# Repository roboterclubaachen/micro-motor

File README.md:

# µMotor: a motor controller for BLDC and DC motors up to 250W

µMotor (or micro-motor) is a motor controller PCB and software made to control any BLDC and DC motor up to 250W.

The micro-motor is supplied with power and CAN bus via a single connector and can control the motor independently.
In addition, a limit switch can be read out and the temperature of the motor can be monitored.

Communication is done via Can-Bus using CANopen protocol.

The software is written using the [modm.io](https://modm.io/) framework and [librobots2](https://github.com/roboterclubaachen/librobots2).

For more information read the following blog posts about the project (in German):
* [µMotor: Idee](http://www.roboterclub.rwth-aachen.de/blog/2018/micro-motor-motorcontroller.html)
* [µMotor: Inbetriebnahme und Debugging](http://www.roboterclub.rwth-aachen.de/blog/2018/micro-motor-debugging-inbetriebnahme.html)
* [µMotor 2 - Teil 1: Konzept](http://www.roboterclub.rwth-aachen.de/blog/2019/micro-motor-2-teil-1.html)
* [µMotor 2 - Teil 2: Strommessung](http://www.roboterclub.rwth-aachen.de/blog/2019/micro-motor-2-teil-2.html)
* [µMotor 2 - Teil 3: Microcontroller & Stromversorgung](http://www.roboterclub.rwth-aachen.de/blog/2019/micro-motor-2-teil-3.html)
* [µMotor 2 - Teil 4: Strom- und Spannungsmessung mit ADC](https://www.roboterclub.rwth-aachen.de/blog/2020/micro-motor-2-teil-4.html)

## Technical data
* 3 phases (BLDC and DC motors)
* Approx. 10A per phase (with precise current measurement)
* 24V nominal operating voltage
* Adjustable cycle-by-cycle current limiting (short circuit protection)
* CAN bus
    * CAN-FD supported
    * CANopen protocoll (partial implemented)
* AB(I) incremental encoder connector
* Hall sensor connector
* Temperature sensor (NTC) connector
* Limit switch (GPIO) connector
* LEDs for status and diagnosis
* Configurable ID (from STM32 hardware ID)
* Easy to solder and assemble

## Status

PCBs *micro-motor-v1 (rev1)* and *macro-motor* are not supported anymore.

The second version *micro-motor-v2* is basically functional, software improvements are in progress.

PCB _micro-motor-v2.1_ is similar to _v2_, but with added RC filters at encoder connector,
added 1 µF capacitor to the STM32 _VREFBUF_ output and changed DC/DC converter modules (caused by component shortage).

Software at HEAD is compatible with micro-motor-v2.\[0,1,2\], however the correct version needs to be selected in the project.xml to account for hardware differences with "Board.v2_1" being compatible with v2.0, and v2.1 and "Board.v2_2" being compatible with v2.2.

## Folder structure

#### `kicad/pcb_name/`
* KiCad files of the PCBs

#### `STM32CubeMX/`
* Pinout configuration of the STM32 microcontrollers done with [STs CubeMX software](https://www.st.com/en/development-tools/stm32cubemx.html)

#### `tests/`
* Test software. Useful during PCB assembly

#### `app/`
* Main Software

#### `src/`
* Common files used between main software and tests.

## Notes

### On first boot
When first assembled the boards will be stuck inside the STM32 bootloader because BOOT0 is used as a GPIO pin.
This behaviour can be overwritten by setting an option byte: \
First read flash option byte:

    openocd -f interface/stlink.cfg -c "transport select hla_swd" -f target/stm32g4x.cfg -c "reset_config none" -c "init" -c "stm32g4x option_read 0 0x20" -c "shutdown"

Should respond 'Option Register: <0x40022020> = 0xffeff8aa' on a new PCB
or 'Option Register: <0x40022020> = 0xfbeff8aa' once the nSWBOOT0 bit is cleared. \
Clear the bit:

    openocd -f interface/stlink.cfg -c "transport select hla_swd" -f target/stm32g4x.cfg -c "reset_config none" -c "init" -c "stm32g4x option_write 0 0x20 0x00000000 0x04000000" -c "shutdown"

## License

Software is licensed under [GPLv3](LICENSE).
Hardware (PCB files, ...) is licensed under [CERN OHL v.1.2](LICENSE.hardware).

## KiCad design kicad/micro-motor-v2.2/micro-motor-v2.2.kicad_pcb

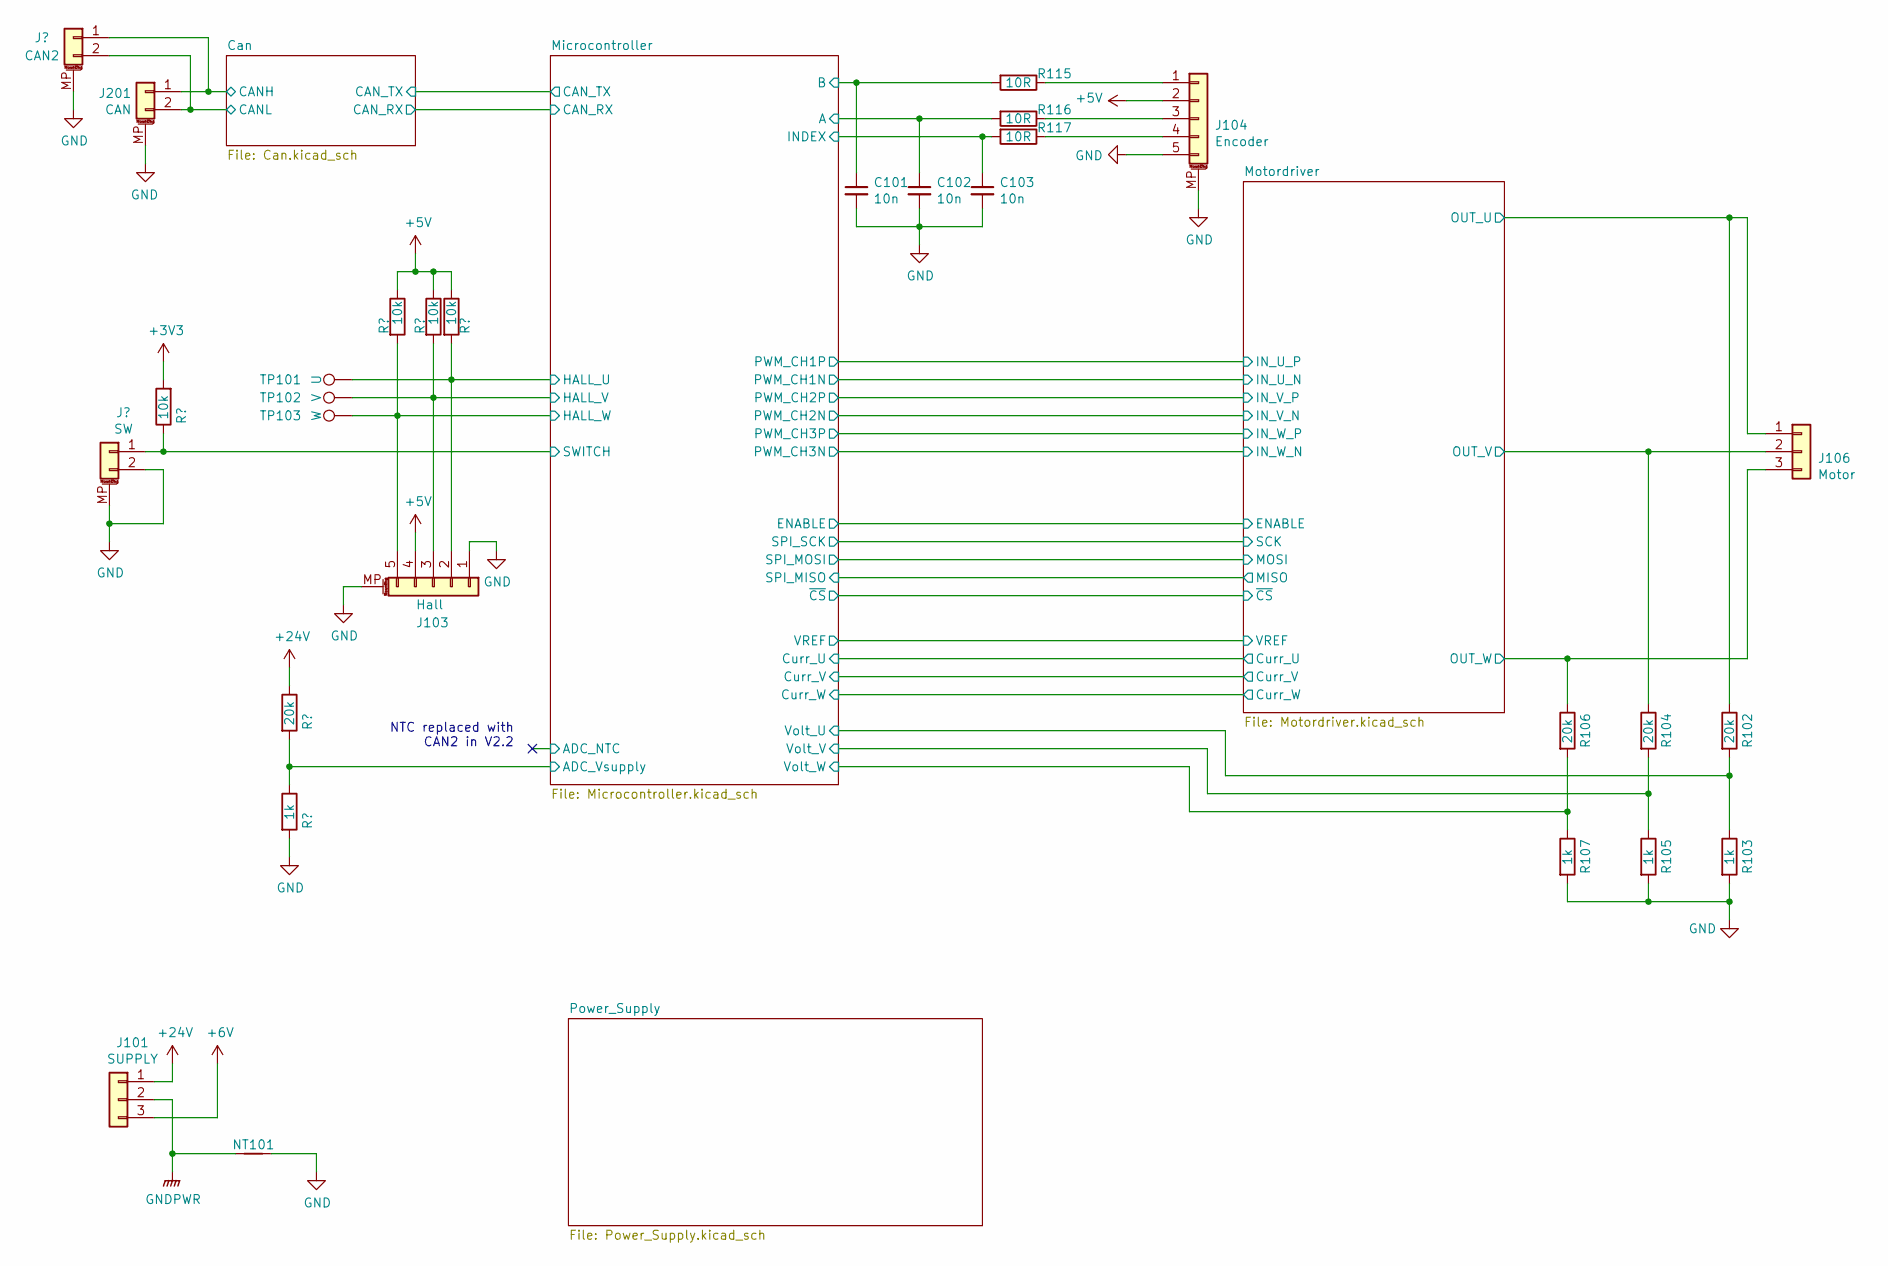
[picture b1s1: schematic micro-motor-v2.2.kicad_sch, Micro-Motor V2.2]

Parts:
C101, C102, C103: 10n; C_0402_1005Metric
J101: SUPPLY; JST_XH_B3B-XH-A_1x03_P2.50mm_Vertical
J102: SW; JST_GH_BM02B-GHS-TBT_1x02-1MP_P1.25mm_Vertical
J103: Hall; JST_GH_BM05B-GHS-TBT_1x05-1MP_P1.25mm_Vertical
J104: Encoder; JST_GH_BM05B-GHS-TBT_1x05-1MP_P1.25mm_Vertical
J105: CAN2; JST_GH_BM02B-GHS-TBT_1x02-1MP_P1.25mm_Vertical
J106: Motor; JST_XH_B3B-XH-A_1x03_P2.50mm_Vertical
J201: CAN; JST_GH_BM02B-GHS-TBT_1x02-1MP_P1.25mm_Vertical
NT101: NetTie_2; NetTie-2_SMD_Pad0.5mm
R101, R111, R112, R113: 10k; R_0402_1005Metric
R102, R104, R106, R109: 20k; R_0402_1005Metric
R103, R105, R107, R110: 1k; R_0402_1005Metric
R115, R116, R117: 10R; R_0402_1005Metric
TP101: U; TestPoint_Pad_D1.0mm
TP102: V; TestPoint_Pad_D1.0mm
TP103: W; TestPoint_Pad_D1.0mm

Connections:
+3V3: R101.2; also elsewhere on the board
+5V: J103.4, J104.2, R111.1, R112.1, R113.1; also elsewhere on the board
+6V: J101.3; also elsewhere on the board
+24V: J101.1, R109.1; also elsewhere on the board
/Can/CANH: J105.1; also elsewhere on the board
/Can/CANL: J105.2; also elsewhere on the board
/Microcontroller/A: C102.1, R116.2; also elsewhere on the board
/Microcontroller/ADC_Vsupply: R109.2, R110.1; also elsewhere on the board
/Microcontroller/B: C101.1, R115.2; also elsewhere on the board
/Microcontroller/HALL_U: J103.2, R113.2, TP101.1; also elsewhere on the board
/Microcontroller/HALL_V: J103.3, R112.2, TP102.1; also elsewhere on the board
/Microcontroller/HALL_W: J103.5, R111.2, TP103.1; also elsewhere on the board
/Microcontroller/INDEX: C103.1, R117.2; also elsewhere on the board
/Microcontroller/SWITCH: J102.1, R101.1; also elsewhere on the board
/Microcontroller/Volt_U: R102.2, R103.1; also elsewhere on the board
/Microcontroller/Volt_V: R104.2, R105.1; also elsewhere on the board
/Microcontroller/Volt_W: R106.2, R107.1; also elsewhere on the board
/Motordriver/OUT_U: J106.1, R102.1; also elsewhere on the board
/Motordriver/OUT_V: J106.2, R104.1; also elsewhere on the board
/Motordriver/OUT_W: J106.3, R106.1; also elsewhere on the board
GND: C101.2, C102.2, C103.2, J102.2, J102.MP (MountPin), J103.1, J103.MP (MountPin), J104.5, J104.MP (MountPin), J105.MP (MountPin), NT101.2, R103.2, R105.2, R107.2, R110.2; also elsewhere on the board
GNDPWR: J101.2, NT101.1; also elsewhere on the board
unnamed: J104.1, R115.1
unnamed: J104.3, R116.1
unnamed: J104.4, R117.1

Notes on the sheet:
NTC replaced with CAN2 in V2.2

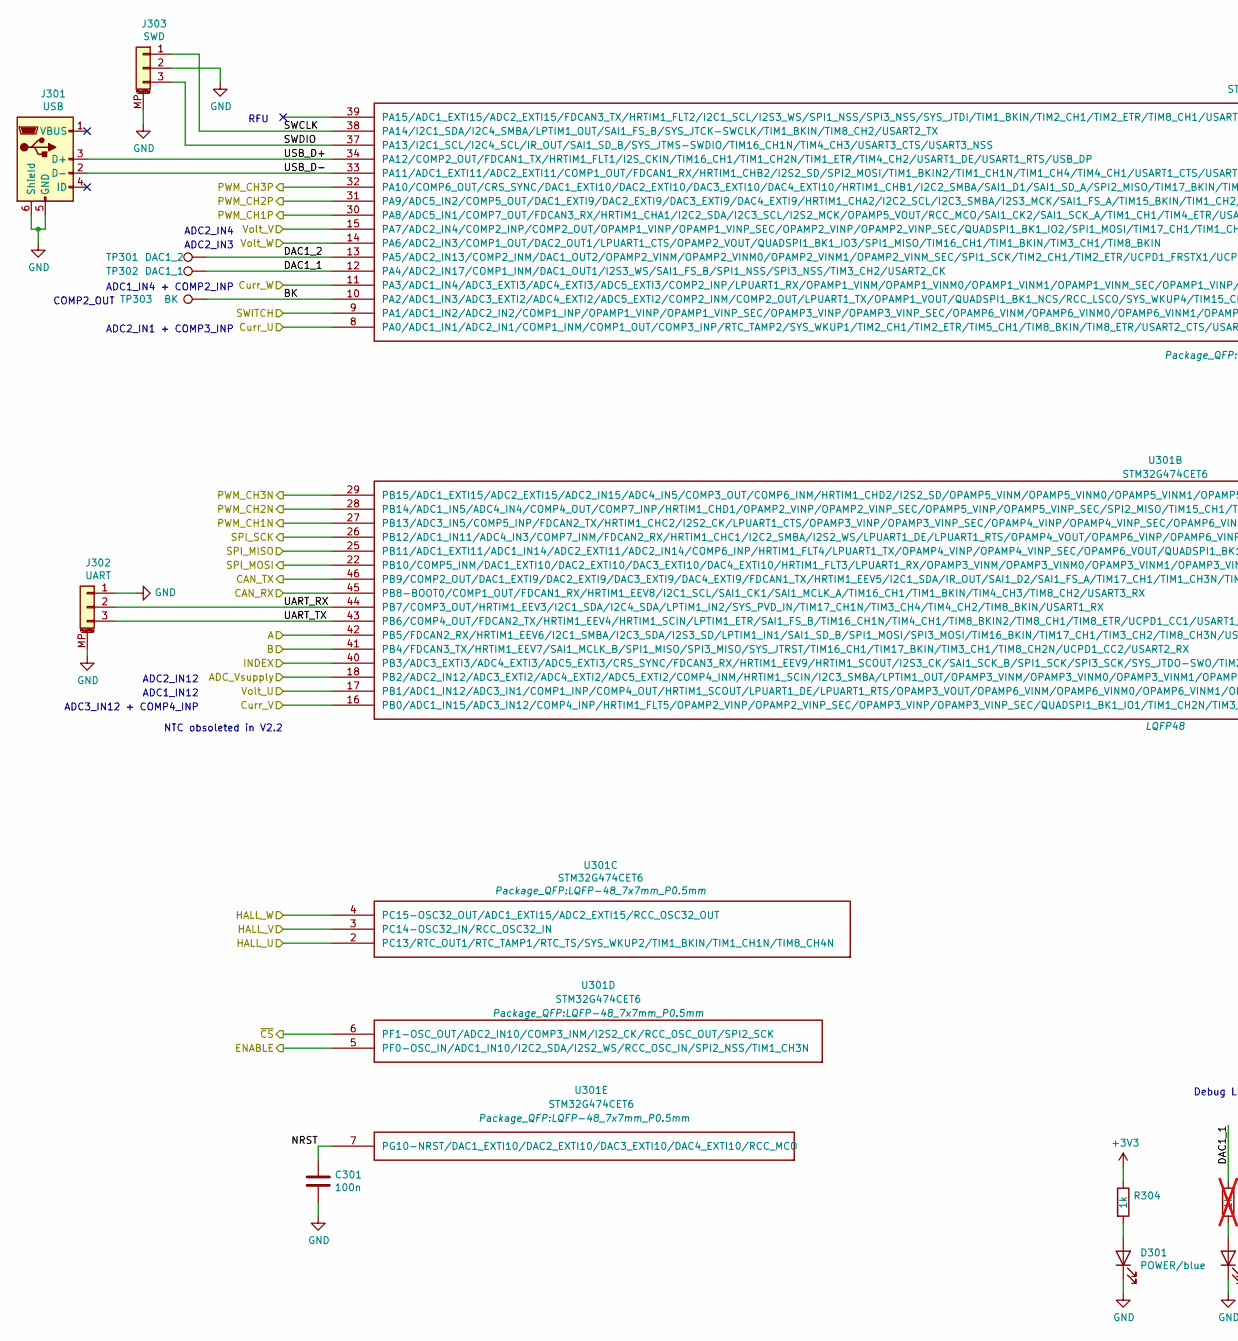
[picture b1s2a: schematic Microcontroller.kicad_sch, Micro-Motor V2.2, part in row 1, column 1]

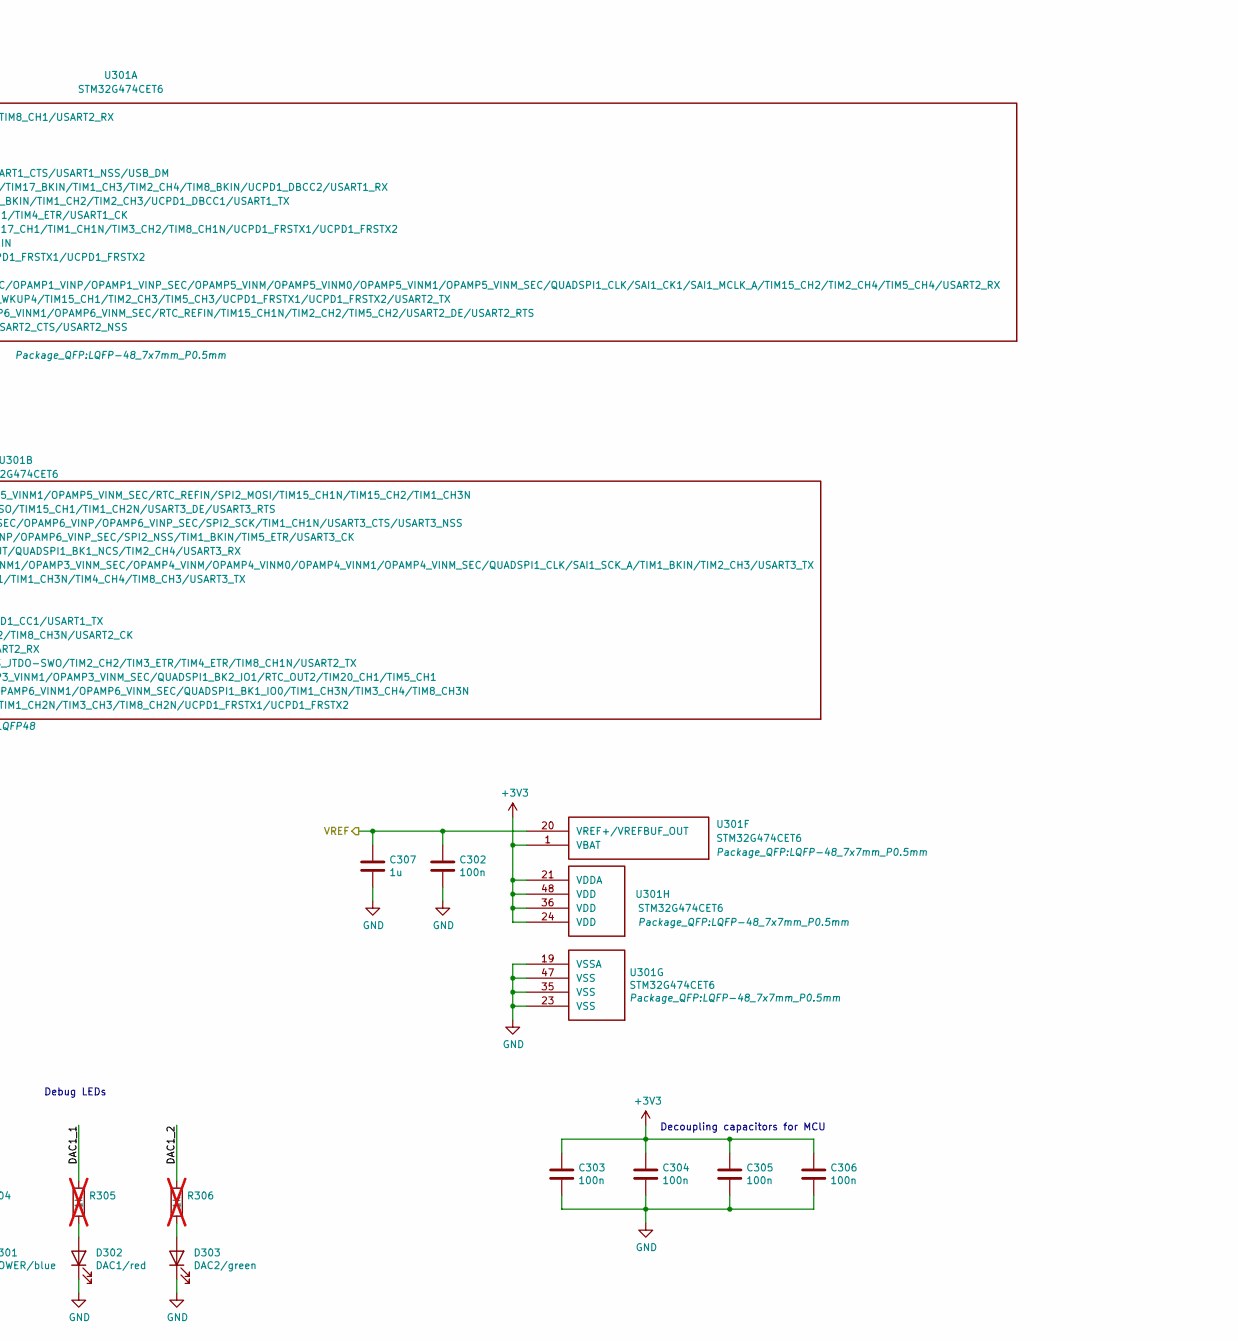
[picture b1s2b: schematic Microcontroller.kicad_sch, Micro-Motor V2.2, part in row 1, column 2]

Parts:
C301, C302, C303, C304, C305, C306: 100n; C_0402_1005Metric
C307: 1u; C_0402_1005Metric
D301: POWER/blue; LED_0402_1005Metric
D302: DAC1/red; LED_0402_1005Metric
D303: DAC2/green; LED_0402_1005Metric
J301: USB; USB_Micro-B_Molex-105133-0001
J302: UART; JST_GH_BM03B-GHS-TBT_1x03-1MP_P1.25mm_Vertical
J303: SWD; JST_GH_BM03B-GHS-TBT_1x03-1MP_P1.25mm_Vertical
R304: 1k; R_0402_1005Metric
R305, R306: 1k; R_0402_1005Metric; not fitted
TP301: DAC1_2; TestPoint_Pad_D1.0mm
TP302: DAC1_1; TestPoint_Pad_D1.0mm
TP303: BK; TestPoint_Pad_D1.0mm
U301: STM32G474CET6; LQFP-48_7x7mm_P0.5mm

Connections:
+3V3: C303.1, C304.1, C305.1, C306.1, R304.1, U301.1 (VBAT), U301.21 (VDDA), U301.24 (VDD), U301.36 (VDD), U301.48 (VDD); also elsewhere on the board
/Can/CAN_RX: U301.45 (PB8-BOOT0/COMP1_OUT/FDCAN1_RX/HRTIM1_EE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); also elsewhere on the board
/Can/CAN_TX: U301.46 (PB9/COMP2_OUT/DAC1_EXTI9/DAC2_EXTI9/DAC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); also elsewhere on the board
/Microcontroller/A: U301.42 (PB5/FDCAN2_RX/HRTIM1_EEV6/I2C1_SMBA/I2C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); also elsewhere on the board
/Microcontroller/ADC_Vsupply: U301.18 (PB2/ADC2_IN12/ADC3_EXTI2/ADC4_EXTI2/ADC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); also elsewhere on the board
/Microcontroller/B: U301.41 (PB4/FDCAN3_TX/HRTIM1_EEV7/SAI1_MCLK_B/S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); also elsewhere on the board
/Microcontroller/BK: TP303.1, U301.10 (PA2/ADC1_IN3/ADC3_EXTI2/ADC4_EXTI2/ADC5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)
/Microcontroller/Curr_U: U301.8 (PA0/ADC1_IN1/ADC2_IN1/COMP1_INM/COMP1_O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); also elsewhere on the board
/Microcontroller/Curr_V: U301.16 (PB0/ADC1_IN15/ADC3_IN12/COMP4_INP/HRTIM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); also elsewhere on the board
/Microcontroller/Curr_W: U301.11 (PA3/ADC1_IN4/ADC3_EXTI3/ADC4_EXTI3/ADC5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); also elsewhere on the board
/Microcontroller/DAC1_1: R305.1, TP302.1, U301.12 (PA4/ADC2_IN17/COMP1_INM/DAC1_OUT1/I2S3_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)
/Microcontroller/DAC1_2: R306.1, TP301.1, U301.13 (PA5/ADC2_IN13/COMP2_INM/DAC1_OUT2/OPAMP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)
/Microcontroller/ENABLE: U301.5 (PF0-OSC_IN/ADC1_IN10/I2C2_SDA/I2S2_WS/R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); also elsewhere on the board
/Microcontroller/HALL_U: U301.2 (PC13/RTC_OUT1/RTC_TAMP1/RTC_TS/SYS_WKUP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); also elsewhere on the board
/Microcontroller/HALL_V: U301.3 (PC14-OSC32_IN/RCC_OSC32_IN); also elsewhere on the board
/Microcontroller/HALL_W: U301.4 (PC15-OSC32_OUT/ADC1_EXTI15/ADC2_EXTI15/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); also elsewhere on the board
/Microcontroller/INDEX: U301.40 (PB3/ADC3_EXTI3/ADC4_EXTI3/ADC5_EXTI3/CR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); also elsewhere on the board
/Microcontroller/NRST: C301.1, U301.7 (PG10-NRST/DAC1_EXTI10/DAC2_EXTI10/DAC3_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)
/Microcontroller/PWM_CH1N: U301.27 (PB13/ADC3_IN5/COMP5_INP/FDCAN2_TX/HRTIM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); also elsewhere on the board
/Microcontroller/PWM_CH1P: U301.30 (PA8/ADC5_IN1/COMP7_OUT/FDCAN3_RX/HRTIM1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); also elsewhere on the board
/Microcontroller/PWM_CH2N: U301.28 (PB14/ADC1_IN5/ADC4_IN4/COMP4_OUT/COMP7_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); also elsewhere on the board
/Microcontroller/PWM_CH2P: U301.31 (PA9/ADC5_IN2/COMP5_OUT/DAC1_EXTI9/DAC2_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); also elsewhere on the board
/Microcontroller/PWM_CH3N: U301.29 (PB15/ADC1_EXTI15/ADC2_EXTI15/ADC2_IN15/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); also elsewhere on the board
/Microcontroller/PWM_CH3P: U301.32 (PA10/COMP6_OUT/CRS_SYNC/DAC1_EXTI10/DAC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); also elsewhere on the board
/Microcontroller/SPI_MISO: U301.25 (PB11/ADC1_EXTI11/ADC1_IN14/ADC2_EXTI11/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); also elsewhere on the board
/Microcontroller/SPI_MOSI: U301.22 (PB10/COMP5_INM/DAC1_EXTI10/DAC2_EXTI10/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); also elsewhere on the board
/Microcontroller/SPI_SCK: U301.26 (PB12/ADC1_IN11/ADC4_IN3/COMP7_INM/FDCAN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); also elsewhere on the board
/Microcontroller/SWCLK: J303.1, U301.38 (PA14/I2C1_SDA/I2C4_SMBA/LPTIM1_OUT/SAI1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)
/Microcontroller/SWDIO: J303.3, U301.37 (PA13/I2C1_SCL/I2C4_SCL/IR_OUT/SAI1_SD_B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)
/Microcontroller/SWITCH: U301.9 (PA1/ADC1_IN2/ADC2_IN2/COMP1_INP/OPAMP1_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); also elsewhere on the board
/Microcontroller/UART_RX: J302.2, U301.44 (PB7/COMP3_OUT/HRTIM1_EEV3/I2C1_SDA/I2C4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)
/Microcontroller/UART_TX: J302.3, U301.43 (PB6/COMP4_OUT/FDCAN2_TX/HRTIM1_EEV4/HRT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)
/Microcontroller/USB_D+: J301.3 (D+), U301.34 (PA12/COMP2_OUT/FDCAN1_TX/HRTIM1_FLT1/I2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)
/Microcontroller/USB_D-: J301.2 (D-), U301.33 (PA11/ADC1_EXTI11/ADC2_EXTI11/COMP1_OUT/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)
/Microcontroller/VREF: C302.1, C307.1, U301.20 (VREF+/VREFBUF_OUT); also elsewhere on the board
/Microcontroller/Volt_U: U301.17 (PB1/ADC1_IN12/ADC3_IN1/COMP1_INP/COMP4_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); also elsewhere on the board
/Microcontroller/Volt_V: U301.15 (PA7/ADC2_IN4/COMP2_INP/COMP2_OUT/OPAMP1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); also elsewhere on the board
/Microcontroller/Volt_W: U301.14 (PA6/ADC2_IN3/COMP1_OUT/DAC2_OUT1/LPUART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); also elsewhere on the board
/Microcontroller/~CS: U301.6 (PF1-OSC_OUT/ADC2_IN10/COMP3_INM/I2S2_CK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); also elsewhere on the board
GND: C301.2, C302.2, C303.2, C304.2, C305.2, C306.2, C307.2, D301.1 (K), D302.1 (K), D303.1 (K), J301.5 (GND), J301.6 (Shield), J302.1, J302.MP (MountPin), J303.2, J303.MP (MountPin), U301.19 (VSSA), U301.23 (VSS), U301.35 (VSS), U301.47 (VSS); also elsewhere on the board
unnamed: D301.2 (A), R304.2
unnamed: D302.2 (A), R305.2
unnamed: D303.2 (A), R306.2

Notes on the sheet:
ADC1_IN4 + COMP2_INP
ADC2_IN3
ADC2_IN12
ADC3_IN12 + COMP4_INP
ADC2_IN4
NTC obsoleted in V2.2
Debug LEDs
Decoupling capacitors for MCU
COMP2_OUT
RFU
ADC1_IN12
ADC2_IN1 + COMP3_INP

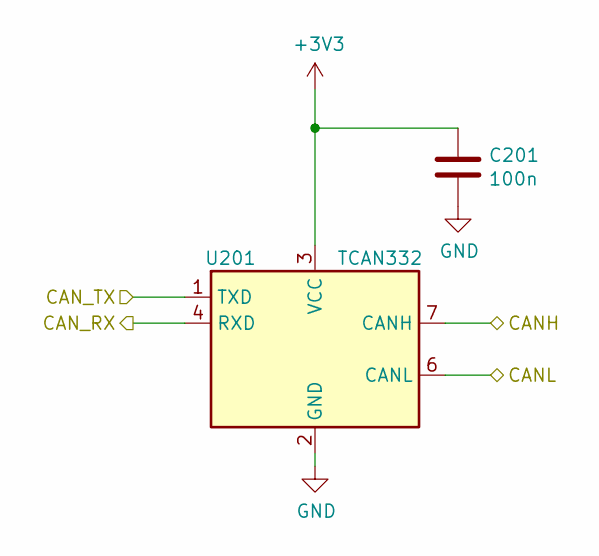
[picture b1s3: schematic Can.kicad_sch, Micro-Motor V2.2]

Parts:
C201: 100n; C_0402_1005Metric
U201: TCAN332; SOT-23-8

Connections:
+3V3: C201.1, U201.3 (VCC); also elsewhere on the board
/Can/CANH: U201.7 (CANH); also elsewhere on the board
/Can/CANL: U201.6 (CANL); also elsewhere on the board
/Can/CAN_RX: U201.4 (RXD); also elsewhere on the board
/Can/CAN_TX: U201.1 (TXD); also elsewhere on the board
GND: C201.2, U201.2 (GND); also elsewhere on the board

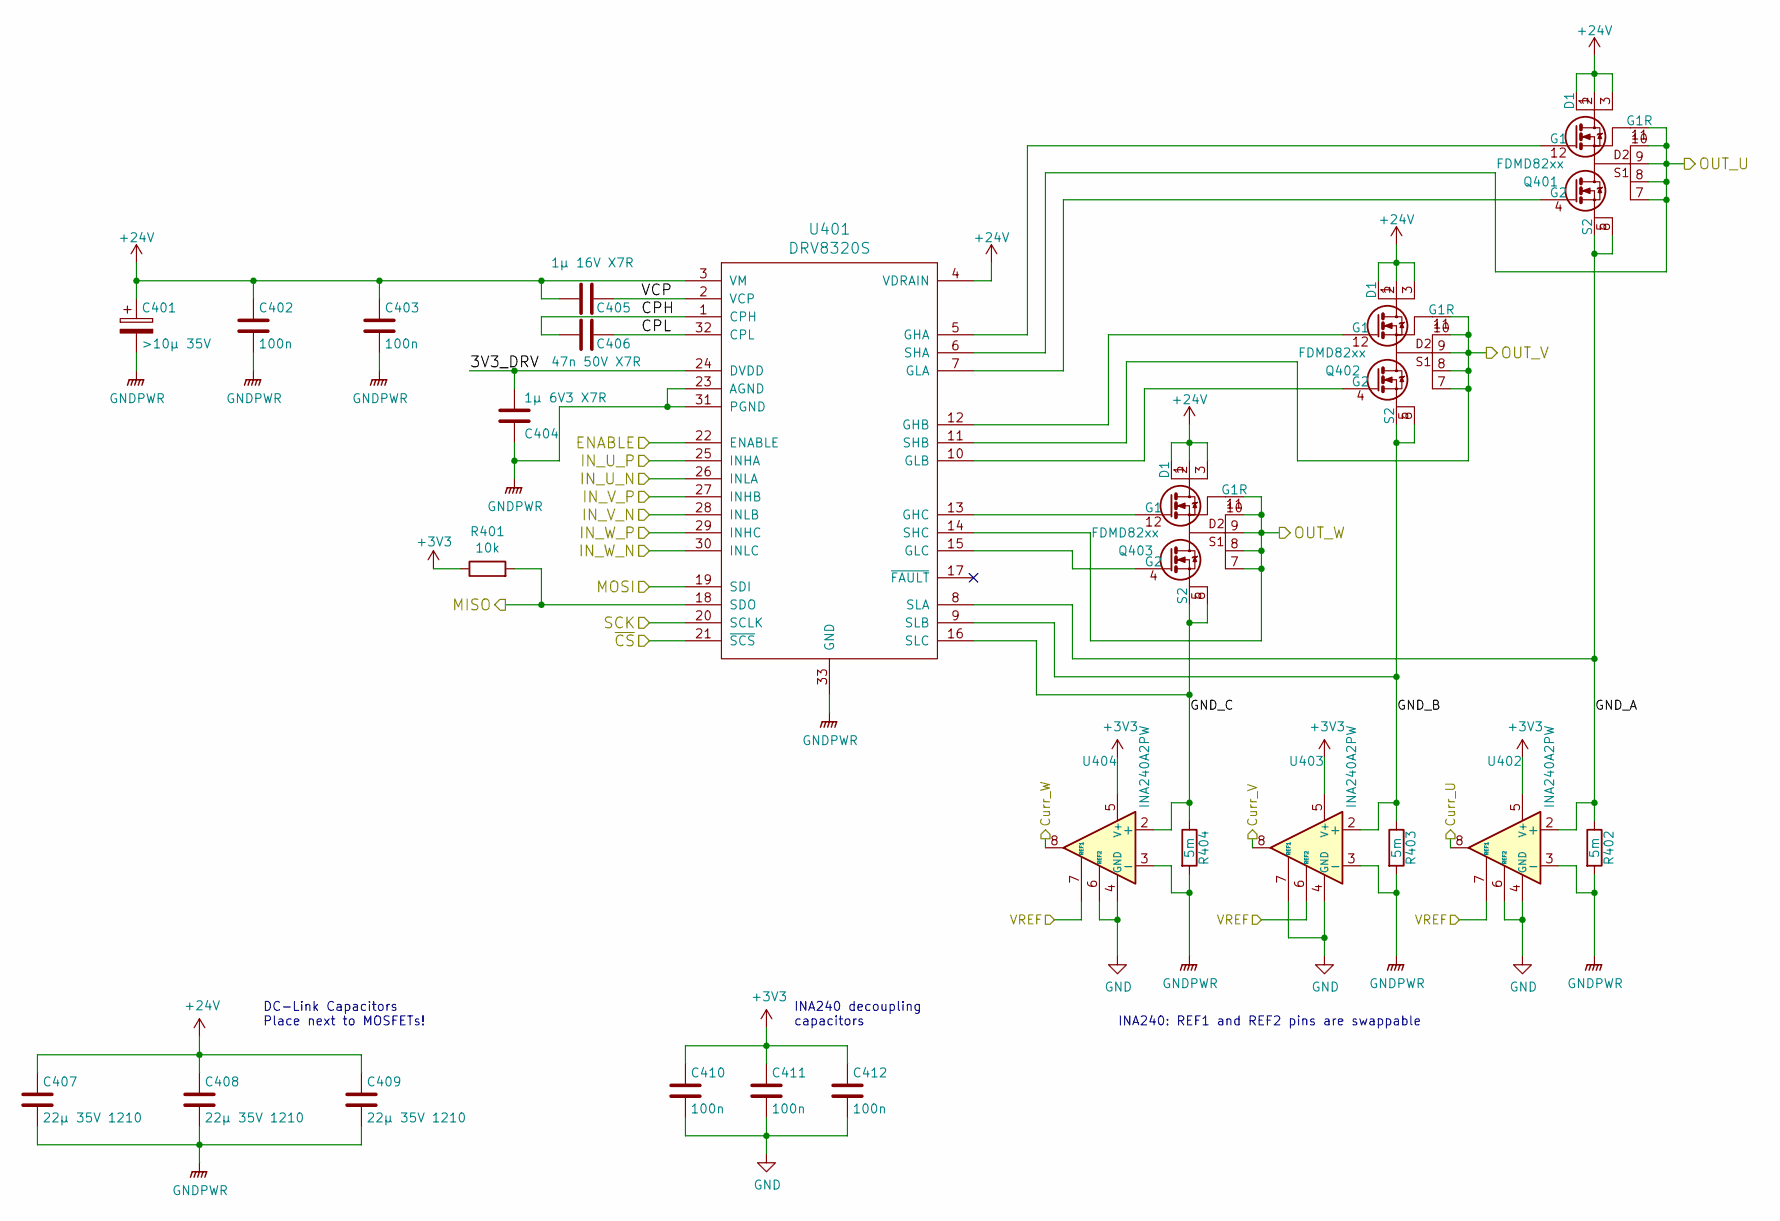
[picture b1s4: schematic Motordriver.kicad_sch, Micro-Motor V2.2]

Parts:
C401: >10µ 35V; CP_Radial_D10.0mm_P5.00mm
C402, C403, C410, C411, C412: 100n; C_0402_1005Metric
C404: 1µ 6V3 X7R; C_0603_1608Metric
C405: 1µ 16V X7R; C_0603_1608Metric
C406: 47n 50V X7R; C_0402_1005Metric
C407, C408, C409: 22µ 35V 1210; C_1210_3225Metric
Q401, Q402, Q403: FDMD82xx; DFN-12-2EP_3.3x5mm_Pitch0.65mm
R401: 10k; R_0402_1005Metric
R402, R403, R404: 5m; R_0805_2012Metric
U401: DRV8320S; QFN-32-1EP_5x5mm_P0.5mm_EP3.45x3.45mm
U402, U403, U404: INA240A2PW; TSSOP-8_4.4x3mm_P0.65mm

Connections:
+3V3: C410.1, C411.1, C412.1, R401.1, U402.5 (V+), U403.5 (V+), U404.5 (V+); also elsewhere on the board
+24V: C401.1, C402.1, C403.1, C405.2, C407.1, C408.1, C409.1, Q401.1 (D1), Q401.2, Q401.3, Q401.13 (D1), Q402.1 (D1), Q402.2, Q402.3, Q402.13 (D1), Q403.1 (D1), Q403.2, Q403.3, Q403.13 (D1), U401.3 (VM), U401.4 (VDRAIN); also elsewhere on the board
/Microcontroller/Curr_U: U402.8; also elsewhere on the board
/Microcontroller/Curr_V: U403.8; also elsewhere on the board
/Microcontroller/Curr_W: U404.8; also elsewhere on the board
/Microcontroller/ENABLE: U401.22 (ENABLE); also elsewhere on the board
/Microcontroller/PWM_CH1N: U401.26 (INLA); also elsewhere on the board
/Microcontroller/PWM_CH1P: U401.25 (INHA); also elsewhere on the board
/Microcontroller/PWM_CH2N: U401.28 (INLB); also elsewhere on the board
/Microcontroller/PWM_CH2P: U401.27 (INHB); also elsewhere on the board
/Microcontroller/PWM_CH3N: U401.30 (INLC); also elsewhere on the board
/Microcontroller/PWM_CH3P: U401.29 (INHC); also elsewhere on the board
/Microcontroller/SPI_MISO: R401.2, U401.18 (SDO); also elsewhere on the board
/Microcontroller/SPI_MOSI: U401.19 (SDI); also elsewhere on the board
/Microcontroller/SPI_SCK: U401.20 (SCLK); also elsewhere on the board
/Microcontroller/VREF: U402.7 (REF1), U403.6 (REF2), U404.7 (REF1); also elsewhere on the board
/Microcontroller/~CS: U401.21 (~SCS); also elsewhere on the board
/Motordriver/3V3_DRV: C404.1, U401.24 (DVDD)
/Motordriver/CPH: C406.2, U401.1 (CPH)
/Motordriver/CPL: C406.1, U401.32 (CPL)
/Motordriver/GND_A: Q401.5 (S2), Q401.6, Q401.14 (S2), R402.1, U401.8 (SLA), U402.2 (+)
/Motordriver/GND_B: Q402.5 (S2), Q402.6, Q402.14 (S2), R403.1, U401.9 (SLB), U403.2 (+)
/Motordriver/GND_C: Q403.5 (S2), Q403.6, Q403.14 (S2), R404.1, U401.16 (SLC), U404.2 (+)
/Motordriver/OUT_U: Q401.7, Q401.8, Q401.9, Q401.10, Q401.11 (G1R), U401.6 (SHA); also elsewhere on the board
/Motordriver/OUT_V: Q402.7, Q402.8, Q402.9, Q402.10, Q402.11 (G1R), U401.11 (SHB); also elsewhere on the board
/Motordriver/OUT_W: Q403.7, Q403.8, Q403.9, Q403.10, Q403.11 (G1R), U401.14 (SHC); also elsewhere on the board
/Motordriver/VCP: C405.1, U401.2 (VCP)
GND: C410.2, C411.2, C412.2, U402.1 (GND), U402.4 (GND), U402.6 (REF2), U403.1 (GND), U403.4 (GND), U403.7 (REF1), U404.1 (GND), U404.4 (GND), U404.6 (REF2); also elsewhere on the board
GNDPWR: C401.2, C402.2, C403.2, C404.2, C407.2, C408.2, C409.2, R402.2, R403.2, R404.2, U401.23 (AGND), U401.31 (PGND), U401.33 (GND), U402.3 (-), U403.3 (-), U404.3 (-); also elsewhere on the board
unnamed: Q401.12 (G1), U401.5 (GHA)
unnamed: Q401.4 (G2), U401.7 (GLA)
unnamed: Q402.12 (G1), U401.12 (GHB)
unnamed: Q402.4 (G2), U401.10 (GLB)
unnamed: Q403.12 (G1), U401.13 (GHC)
unnamed: Q403.4 (G2), U401.15 (GLC)

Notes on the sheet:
DC-Link Capacitors Place next to MOSFETs!
INA240 decoupling capacitors
INA240: REF1 and REF2 pins are swappable

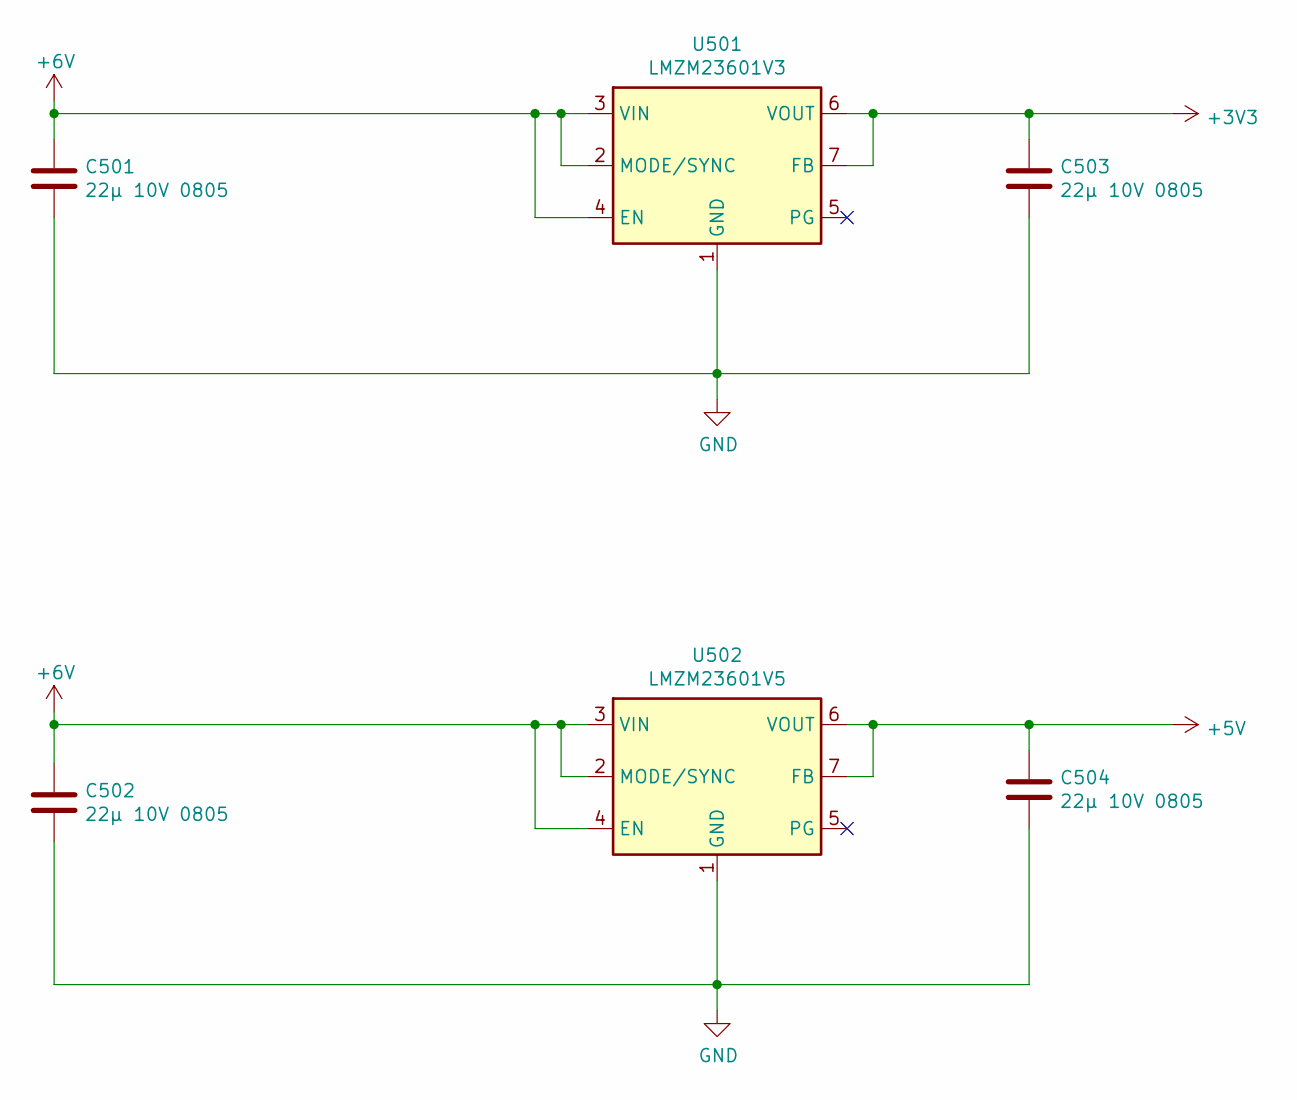
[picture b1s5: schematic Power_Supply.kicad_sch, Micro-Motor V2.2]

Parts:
C501, C502, C503, C504: 22µ 10V 0805; C_0805_2012Metric
U501: LMZM23601V3; Texas_SIL0010A_MicroSiP-10-1EP_3.8x3mm_P0.6mm_EP0.7x2.9mm
U502: LMZM23601V5; Texas_SIL0010A_MicroSiP-10-1EP_3.8x3mm_P0.6mm_EP0.7x2.9mm

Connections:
+3V3: C503.1, U501.6 (VOUT), U501.7 (FB); also elsewhere on the board
+5V: C504.1, U502.6 (VOUT), U502.7 (FB); also elsewhere on the board
+6V: C501.1, C502.1, U501.2 (MODE/SYNC), U501.3 (VIN), U501.4 (EN), U502.2 (MODE/SYNC), U502.3 (VIN), U502.4 (EN); also elsewhere on the board
GND: C501.2, C502.2, C503.2, C504.2, U501.1 (GND), U501.11 (GND), U502.1 (GND), U502.11 (GND); also elsewhere on the board

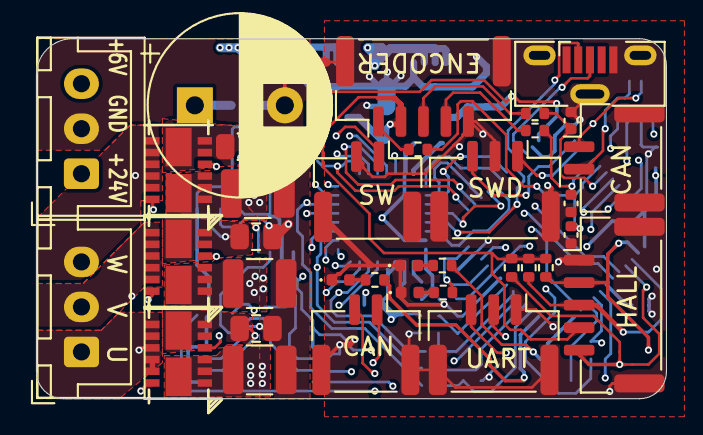
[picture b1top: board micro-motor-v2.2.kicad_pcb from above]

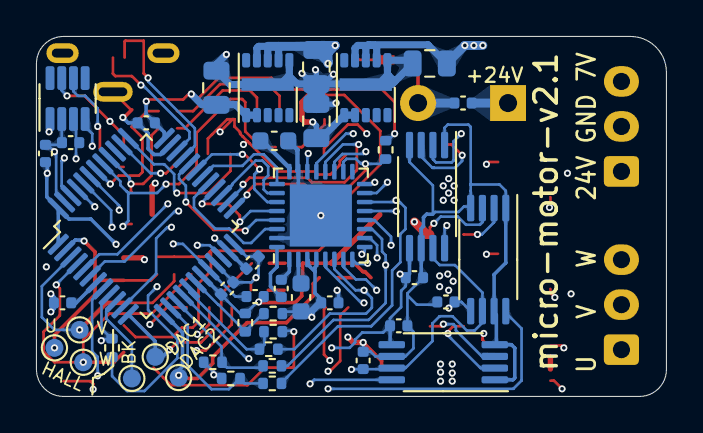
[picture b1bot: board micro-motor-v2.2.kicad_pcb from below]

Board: 4 copper layers, 35.0 x 20.0 mm, 80 parts (44 on the bottom side), 68 nets.

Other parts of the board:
J107: CAN; JST_GH_BM02B-GHS-TBT_1x02-1MP_P1.25mm_Vertical

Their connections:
/Can/CANH: J107.1; also elsewhere on the board
/Can/CANL: J107.2; also elsewhere on the board
GND: J107.MP (MountPin); also elsewhere on the board

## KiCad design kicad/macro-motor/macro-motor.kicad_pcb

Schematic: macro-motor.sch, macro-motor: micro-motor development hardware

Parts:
C101: 4µ7 16V; C_0603_1608Metric
C102, C103: 2µ2 6V3; C_0402_1005Metric
J101: CAN+PWR; PinHeader_1x05_P2.54mm_Vertical
J102: 3V3; Pin_D1.0mm_L10.0mm
J103: 5V; Pin_D1.0mm_L10.0mm
J104: GND; Pin_D1.0mm_L10.0mm
J105: Gpio; Pin_D1.0mm_L10.0mm
J106: U; Pin_D1.0mm_L10.0mm
J107: V; Pin_D1.0mm_L10.0mm
J108: W; Pin_D1.0mm_L10.0mm
J109: Conn_01x03_Female; TerminalBlock_Phoenix_PT-1,5-3-3.5-H_1x03_P3.50mm_Horizontal
J110: HALL; PinHeader_1x05_P2.54mm_Vertical
J111: Fault; Pin_D1.0mm_L10.0mm
R101: 10k; R_0402_1005Metric
R102, R103, R104: 1k; R_0402_1005Metric
R105, R106, R107: 20k; R_0402_1005Metric
R108: (10k); R_0402_1005Metric
U101: ADP7112ACBZ-3.3-R7; WLCSP-6_1.4x1.0mm_P0.4mm
U102: ADP7112ACBZ-5.0-R7; WLCSP-6_1.4x1.0mm_P0.4mm

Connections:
+3V3: C102.1, J102.1, R101.2, R108.1, U101.A2, U101.B2; also elsewhere on the board
+5V: C103.1, J103.1, J110.4, U102.A2, U102.B2; also elsewhere on the board
+6V: C101.1, J101.4, U101.A1, U101.C1, U102.A1, U102.C1
+24V: J101.5; also elsewhere on the board
/CAN/CAN_H: J101.2; also elsewhere on the board
/CAN/CAN_L: J101.1; also elsewhere on the board
/Microcontroller/BemfU: R104.1, R105.2; also elsewhere on the board
/Microcontroller/BemfV: R103.1, R106.2; also elsewhere on the board
/Microcontroller/BemfW: R102.1, R107.2; also elsewhere on the board
/Microcontroller/Fault: J111.1, R108.2; also elsewhere on the board
/Microcontroller/Gpio: J105.1, R101.1; also elsewhere on the board
/Microcontroller/HallU: J106.1, J110.2; also elsewhere on the board
/Microcontroller/HallV: J107.1, J110.3; also elsewhere on the board
/Microcontroller/HallW: J108.1, J110.5; also elsewhere on the board
/Motor_Driver/OUT_U: J109.1, R105.1; also elsewhere on the board
/Motor_Driver/OUT_V: J109.2, R106.1; also elsewhere on the board
/Motor_Driver/OUT_W: J109.3, R107.1; also elsewhere on the board
GND: C101.2, C102.2, C103.2, J101.3, J104.1, J110.1, R102.2, R103.2, R104.2, U101.C2, U102.C2; also elsewhere on the board

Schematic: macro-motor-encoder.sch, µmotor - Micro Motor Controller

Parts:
C201, C206: 100n; C_0402_1005Metric
C202, C203, C204, C205: (2n7); C_0402_1005Metric
J202: B; Pin_D1.0mm_L10.0mm
J203: A; Pin_D1.0mm_L10.0mm
J204: Encoder; PinHeader_1x06_P2.54mm_Vertical
R203, R204, R205, R206: 47k; R_0402_1005Metric
RN201: (2k7); EXB18V
RN202: (100); EXB18V
U201, U202: ISL3280E; SOT-23-5

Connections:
+3V3: C201.1, C206.1, U201.1, U202.1; also elsewhere on the board
+5V: J204.4, R203.1, R205.1, RN201.1, RN201.2, RN201.3, RN201.4; also elsewhere on the board
/Encoder/A: J203.1, U202.3; also elsewhere on the board
/Encoder/B: J202.1, U201.3; also elsewhere on the board
GND: C201.2, C202.1, C203.1, C204.1, C205.1, C206.2, J204.3, R204.2, R206.2, U201.2, U202.2; also elsewhere on the board
unnamed: C202.2, RN202.5, U202.5
unnamed: C203.2, RN202.7, U201.5
unnamed: C204.2, RN202.6, U202.4
unnamed: C205.2, RN202.8, U201.4
unnamed: J204.1, R205.2, R206.1, RN201.6, RN202.3
unnamed: J204.2, RN201.5, RN202.4
unnamed: J204.5, RN201.7, RN202.2
unnamed: J204.6, R203.2, R204.1, RN201.8, RN202.1

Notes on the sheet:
5V/2 high-impedance voltage divider (If pins 1 and 6 are not connected)

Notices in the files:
src/hardware_rev1.hpp:
Copyright (C) 2018 Raphael Lehmann <raphael@rleh.de>
This program is free software: you can redistribute it and/or modify
it under the terms of the GNU General Public License as published by
the Free Software Foundation, either version 3 of the License, or
(at your option) any later version.
src/hardware_v2.hpp:
Copyright (C) 2019 Raphael Lehmann <raphael@rleh.de>
kicad/macro-motor/macro-motor.kicad_pcb:
©Raphael Lehmann
